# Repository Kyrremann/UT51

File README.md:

UT51
====

> Hot-swappable nordic 40% Keyboard PCB

The UT51 is a clone of the UT47.2 with an added cloumn for nordic letters. This also enables the use of the traditional
arrow keys.

Keyboard Layout Editor layout: [UT51 Layout](http://www.keyboard-layout-editor.com/#/gists/70864930e7721bd26d8b0cc32576811b)

## Diary

### [rev1] - 2020-04-10

About two weeks ago I finally sat down and created the extended UT47.2 board that I wanted to make. It was some work, as
I had messed up the footprint by updating them to a newer version. Also since I had to move all the components for the
micro controller, I had to create most of the traces a new. I've now gotten the product back from production, but
haven't had time to solder it yet.

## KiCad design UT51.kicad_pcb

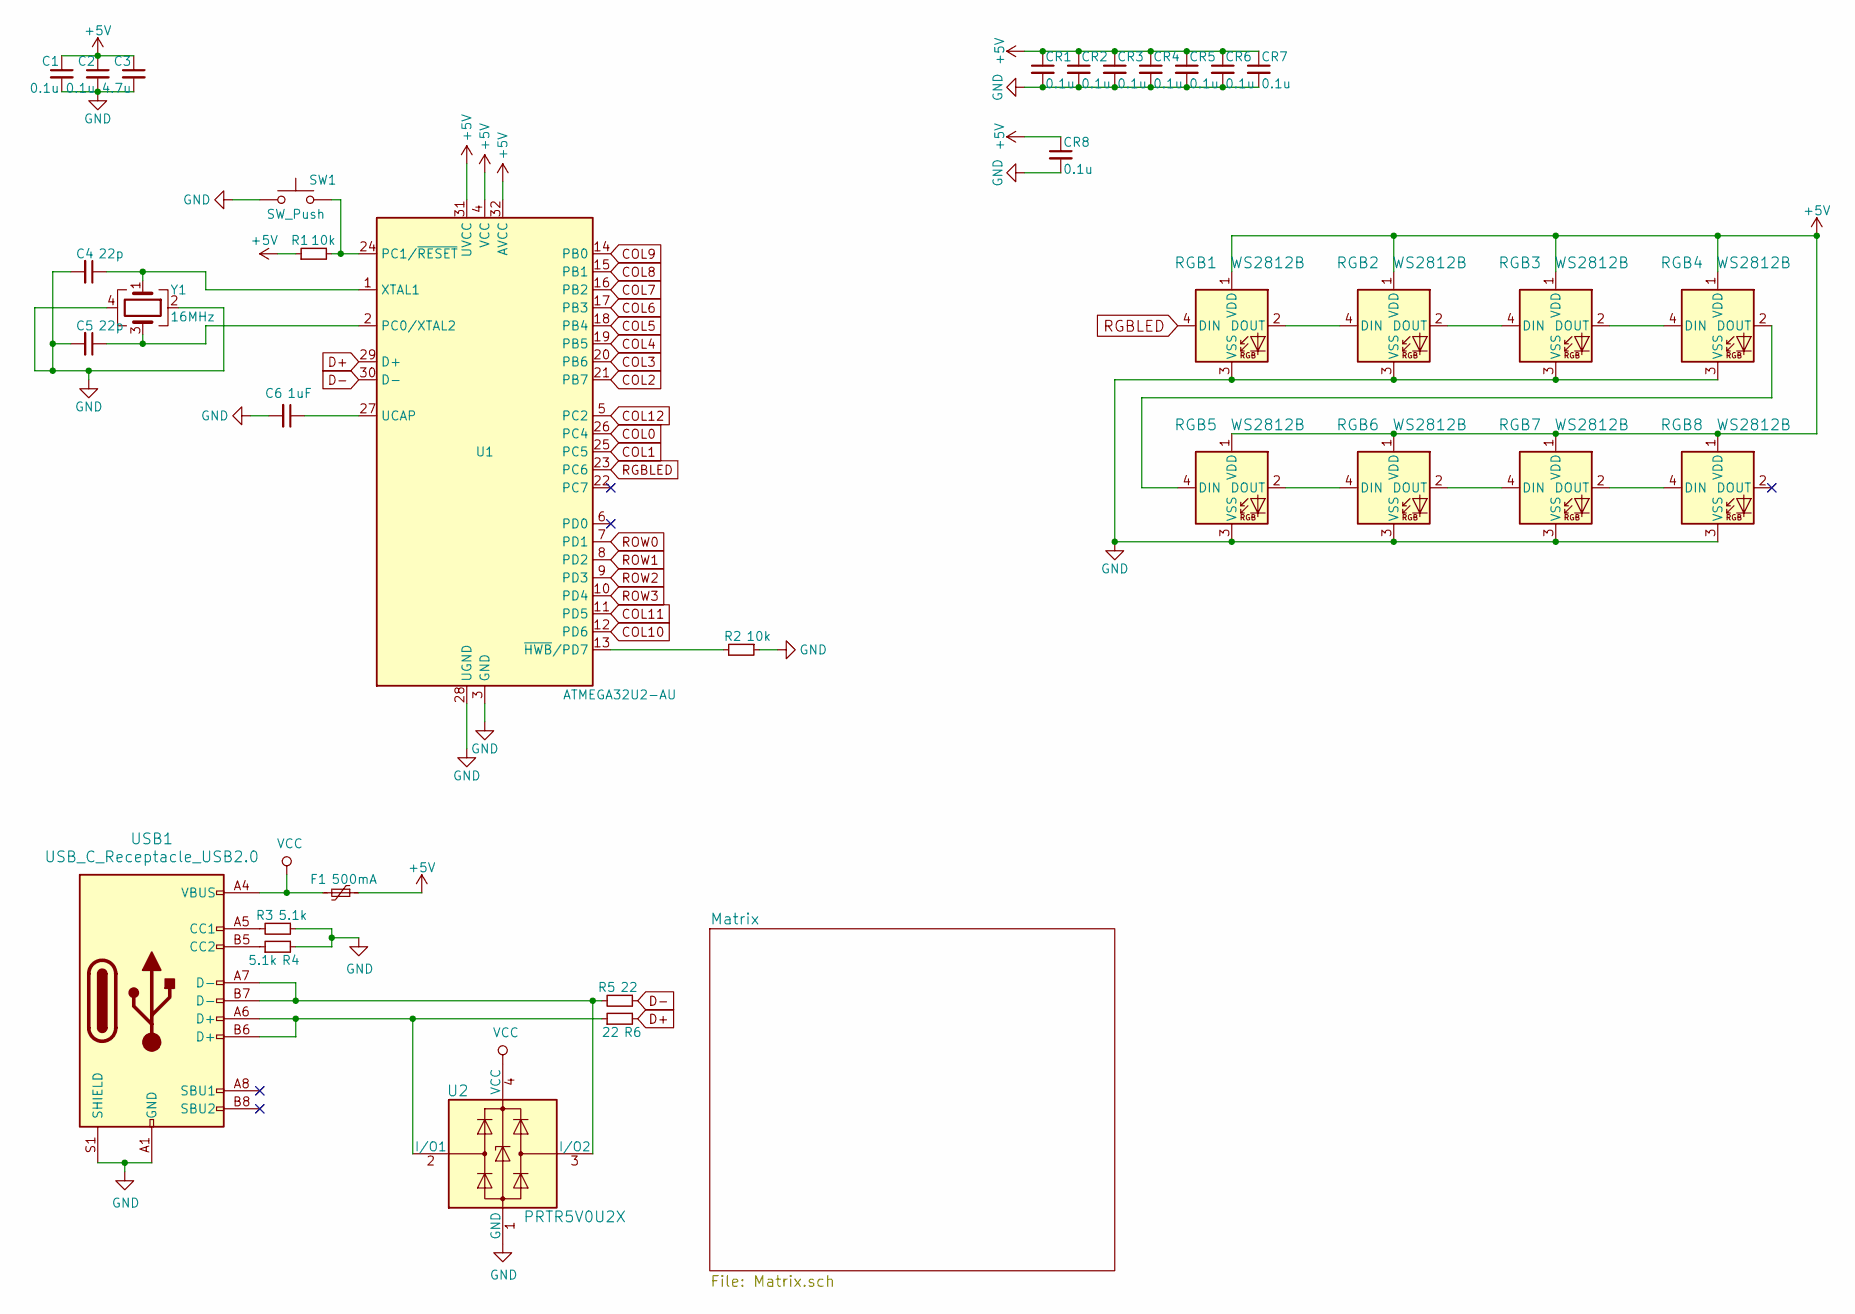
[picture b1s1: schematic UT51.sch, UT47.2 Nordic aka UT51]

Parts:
C1, C2: 0.1u; C_0603_1608Metric
C3: 4.7u; C_0603_1608Metric
C4, C5: 22p; C_0603_1608Metric
C6: 1uF; C_0603_1608Metric
CR1, CR2, CR3, CR4, CR5, CR6, CR7, CR8: 0.1u; C_0603_1608Metric
F1: 500mA; Fuse_0603_1608Metric
R1, R2: 10k; R_0603_1608Metric
R3, R4: 5.1k; R_0603_1608Metric
R5, R6: 22; R_0603_1608Metric
RGB1, RGB2, RGB3, RGB4, RGB5, RGB6, RGB7, RGB8: WS2812B; LED_WS2812B_PLCC4_5.0x5.0mm_P3.2mm
SW1: SW_Push; SW_SPST_CK_RS282G05A3
U1: ATMEGA32U2-AU; QFN-32-1EP_5x5mm_P0.5mm_EP3.1x3.1mm
U2: PRTR5V0U2X; SOT-143B
USB1: USB_C_Receptacle_USB2.0; USB_C_Receptacle_HRO_TYPE-C-31-M-12
Y1: 16MHz; Crystal_SMD_3225-4Pin_3.2x2.5mm_HandSoldering

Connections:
+5V: C1.1, C2.1, C3.1, CR1.1, CR2.1, CR3.1, CR4.1, CR5.1, CR6.1, CR7.1, CR8.1, F1.1, R1.1, RGB1.1 (VDD), RGB2.1 (VDD), RGB3.1 (VDD), RGB4.1 (VDD), RGB5.1 (VDD), RGB6.1 (VDD), RGB7.1 (VDD), RGB8.1 (VDD), U1.4 (VCC), U1.31 (UVCC), U1.32 (AVCC)
COL0: U1.26 (PC4); also elsewhere on the board
COL1: U1.25 (PC5); also elsewhere on the board
COL2: U1.21 (PB7); also elsewhere on the board
COL3: U1.20 (PB6); also elsewhere on the board
COL4: U1.19 (PB5); also elsewhere on the board
COL5: U1.18 (PB4); also elsewhere on the board
COL6: U1.17 (PB3); also elsewhere on the board
COL7: U1.16 (PB2); also elsewhere on the board
COL8: U1.15 (PB1); also elsewhere on the board
COL9: U1.14 (PB0); also elsewhere on the board
COL10: U1.12 (PD6); also elsewhere on the board
COL11: U1.11 (PD5); also elsewhere on the board
COL12: U1.5 (PC2); also elsewhere on the board
D+: R6.2, U1.29 (D+)
D-: R5.1, U1.30 (D-)
GND: C1.2, C2.2, C3.2, C4.2, C5.2, C6.2, CR1.2, CR2.2, CR3.2, CR4.2, CR5.2, CR6.2, CR7.2, CR8.2, R2.1, R3.1, R4.2, RGB1.3 (VSS), RGB2.3 (VSS), RGB3.3 (VSS), RGB4.3 (VSS), RGB5.3 (VSS), RGB6.3 (VSS), RGB7.3 (VSS), RGB8.3 (VSS), SW1.1, U1.3 (GND), U1.28 (UGND), U1.33 (GND), U2.1 (GND), USB1.A1 (GND), USB1.A12 (GND), USB1.B1 (GND), USB1.B12 (GND), USB1.S1 (SHIELD), Y1.2, Y1.4
unnamed: C4.1, U1.1 (XTAL1), Y1.1
unnamed: C5.1, U1.2 (PC0/XTAL2), Y1.3
unnamed: C6.1, U1.27 (UCAP)
unnamed: R1.2, SW1.2, U1.24 (PC1/~RESET)
unnamed: R2.2, U1.13 (~HWB~/PD7)
unnamed: R3.2, USB1.A5 (CC1)
unnamed: R4.1, USB1.B5 (CC2)
unnamed: R5.2, U2.3 (I/O2), USB1.A7 (D-), USB1.B7 (D-)
unnamed: R6.1, U2.2 (I/O1), USB1.A6 (D+), USB1.B6 (D+)
unnamed: RGB1.2 (DOUT), RGB2.4 (DIN)
unnamed: RGB2.2 (DOUT), RGB3.4 (DIN)
unnamed: RGB3.2 (DOUT), RGB4.4 (DIN)
unnamed: RGB4.2 (DOUT), RGB5.4 (DIN)
unnamed: RGB5.2 (DOUT), RGB6.4 (DIN)
unnamed: RGB6.2 (DOUT), RGB7.4 (DIN)
unnamed: RGB7.2 (DOUT), RGB8.4 (DIN)
RGBLED: RGB1.4 (DIN), U1.23 (PC6)
ROW0: U1.7 (PD1); also elsewhere on the board
ROW1: U1.8 (PD2); also elsewhere on the board
ROW2: U1.9 (PD3); also elsewhere on the board
ROW3: U1.10 (PD4); also elsewhere on the board
VCC: F1.2, U2.4 (VCC), USB1.A4 (VBUS), USB1.A9 (VBUS), USB1.B4 (VBUS), USB1.B9 (VBUS)

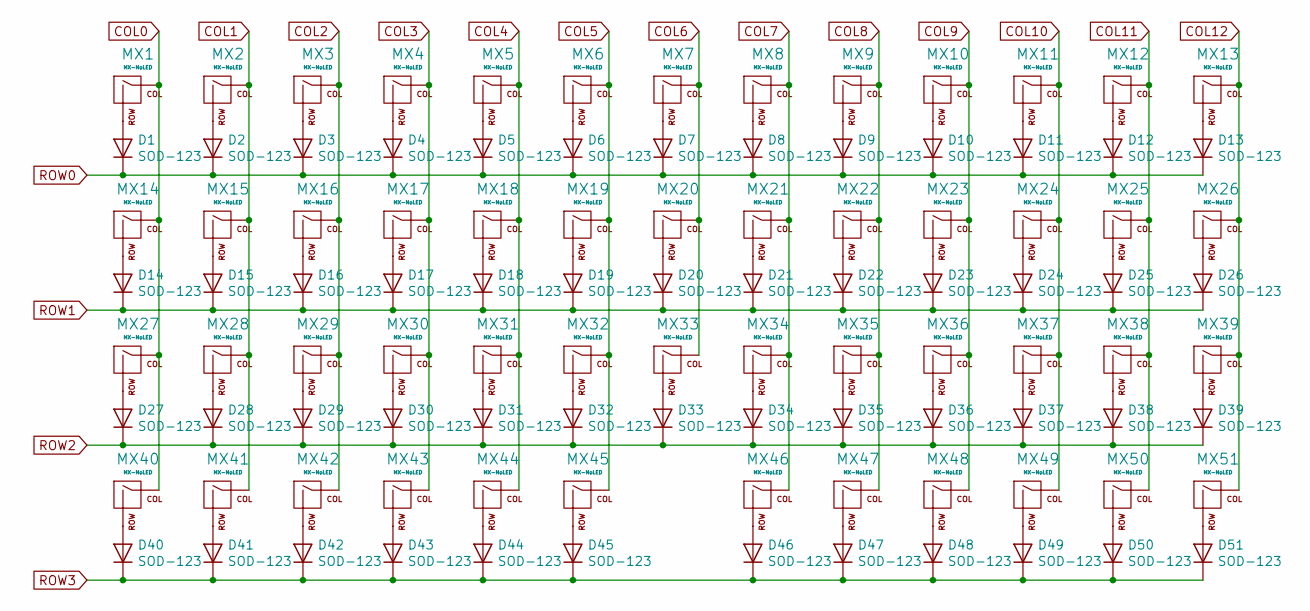
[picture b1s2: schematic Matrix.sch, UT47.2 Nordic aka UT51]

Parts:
D1, D2, D3, D4, D5, D6, D7, D8, D9, D10, D11, D12, D13, D14, D15, D16, D17, D18, D19, D20, D21, D22, D23, D24, D25, D26, D27, D28, D29, D30, D31, D32, D33, D34, D35, D36, D37, D38, D39, D40, D41, D42, D43, D44, D45, D46, D47, D48, D49, D50, D51: SOD-123; D_SOD-123
MX1, MX2, MX3, MX4, MX5, MX6, MX7, MX8, MX9, MX10, MX11, MX12, MX13, MX14, MX15, MX16, MX17, MX18, MX19, MX20, MX21, MX22, MX23, MX24, MX25, MX26, MX27, MX28, MX29, MX30, MX31, MX32, MX33, MX34, MX35, MX36, MX37, MX38, MX39, MX40, MX41, MX42, MX43, MX44, MX45, MX46, MX47, MX48, MX49, MX50, MX51: MX-NoLED; Kailh_socket_MX

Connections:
COL0: MX1.1 (COL), MX14.1 (COL), MX27.1 (COL), MX40.1 (COL); also elsewhere on the board
COL1: MX2.1 (COL), MX15.1 (COL), MX28.1 (COL), MX41.1 (COL); also elsewhere on the board
COL2: MX3.1 (COL), MX16.1 (COL), MX29.1 (COL), MX42.1 (COL); also elsewhere on the board
COL3: MX4.1 (COL), MX17.1 (COL), MX30.1 (COL), MX43.1 (COL); also elsewhere on the board
COL4: MX5.1 (COL), MX18.1 (COL), MX31.1 (COL), MX44.1 (COL); also elsewhere on the board
COL5: MX6.1 (COL), MX19.1 (COL), MX32.1 (COL), MX45.1 (COL); also elsewhere on the board
COL6: MX7.1 (COL), MX20.1 (COL), MX33.1 (COL); also elsewhere on the board
COL7: MX8.1 (COL), MX21.1 (COL), MX34.1 (COL), MX46.1 (COL); also elsewhere on the board
COL8: MX9.1 (COL), MX22.1 (COL), MX35.1 (COL), MX47.1 (COL); also elsewhere on the board
COL9: MX10.1 (COL), MX23.1 (COL), MX36.1 (COL), MX48.1 (COL); also elsewhere on the board
COL10: MX11.1 (COL), MX24.1 (COL), MX37.1 (COL), MX49.1 (COL); also elsewhere on the board
COL11: MX12.1 (COL), MX25.1 (COL), MX38.1 (COL), MX50.1 (COL); also elsewhere on the board
COL12: MX13.1 (COL), MX26.1 (COL), MX39.1 (COL), MX51.1 (COL); also elsewhere on the board
unnamed: D1.2 (A), MX1.2 (ROW)
unnamed: D2.2 (A), MX2.2 (ROW)
unnamed: D3.2 (A), MX3.2 (ROW)
unnamed: D4.2 (A), MX4.2 (ROW)
unnamed: D5.2 (A), MX5.2 (ROW)
unnamed: D6.2 (A), MX6.2 (ROW)
unnamed: D7.2 (A), MX7.2 (ROW)
unnamed: D8.2 (A), MX8.2 (ROW)
unnamed: D9.2 (A), MX9.2 (ROW)
unnamed: D10.2 (A), MX10.2 (ROW)
unnamed: D11.2 (A), MX11.2 (ROW)
unnamed: D12.2 (A), MX12.2 (ROW)
unnamed: D13.2 (A), MX13.2 (ROW)
unnamed: D14.2 (A), MX14.2 (ROW)
unnamed: D15.2 (A), MX15.2 (ROW)
unnamed: D16.2 (A), MX16.2 (ROW)
unnamed: D17.2 (A), MX17.2 (ROW)
unnamed: D18.2 (A), MX18.2 (ROW)
unnamed: D19.2 (A), MX19.2 (ROW)
unnamed: D20.2 (A), MX20.2 (ROW)
unnamed: D21.2 (A), MX21.2 (ROW)
unnamed: D22.2 (A), MX22.2 (ROW)
unnamed: D23.2 (A), MX23.2 (ROW)
unnamed: D24.2 (A), MX24.2 (ROW)
unnamed: D25.2 (A), MX25.2 (ROW)
unnamed: D26.2 (A), MX26.2 (ROW)
unnamed: D27.2 (A), MX27.2 (ROW)
unnamed: D28.2 (A), MX28.2 (ROW)
unnamed: D29.2 (A), MX29.2 (ROW)
unnamed: D30.2 (A), MX30.2 (ROW)
unnamed: D31.2 (A), MX31.2 (ROW)
unnamed: D32.2 (A), MX32.2 (ROW)
unnamed: D33.2 (A), MX33.2 (ROW)
unnamed: D34.2 (A), MX34.2 (ROW)
unnamed: D35.2 (A), MX35.2 (ROW)
unnamed: D36.2 (A), MX36.2 (ROW)
unnamed: D37.2 (A), MX37.2 (ROW)
unnamed: D38.2 (A), MX38.2 (ROW)
unnamed: D39.2 (A), MX39.2 (ROW)
unnamed: D40.2 (A), MX40.2 (ROW)
unnamed: D41.2 (A), MX41.2 (ROW)
unnamed: D42.2 (A), MX42.2 (ROW)
unnamed: D43.2 (A), MX43.2 (ROW)
unnamed: D44.2 (A), MX44.2 (ROW)
unnamed: D45.2 (A), MX45.2 (ROW)
unnamed: D46.2 (A), MX46.2 (ROW)
unnamed: D47.2 (A), MX47.2 (ROW)
unnamed: D48.2 (A), MX48.2 (ROW)
unnamed: D49.2 (A), MX49.2 (ROW)
unnamed: D50.2 (A), MX50.2 (ROW)
unnamed: D51.2 (A), MX51.2 (ROW)
ROW0: D1.1 (K), D2.1 (K), D3.1 (K), D4.1 (K), D5.1 (K), D6.1 (K), D7.1 (K), D8.1 (K), D9.1 (K), D10.1 (K), D11.1 (K), D12.1 (K), D13.1 (K); also elsewhere on the board
ROW1: D14.1 (K), D15.1 (K), D16.1 (K), D17.1 (K), D18.1 (K), D19.1 (K), D20.1 (K), D21.1 (K), D22.1 (K), D23.1 (K), D24.1 (K), D25.1 (K), D26.1 (K); also elsewhere on the board
ROW2: D27.1 (K), D28.1 (K), D29.1 (K), D30.1 (K), D31.1 (K), D32.1 (K), D33.1 (K), D34.1 (K), D35.1 (K), D36.1 (K), D37.1 (K), D38.1 (K), D39.1 (K); also elsewhere on the board
ROW3: D40.1 (K), D41.1 (K), D42.1 (K), D43.1 (K), D44.1 (K), D45.1 (K), D46.1 (K), D47.1 (K), D48.1 (K), D49.1 (K), D50.1 (K), D51.1 (K); also elsewhere on the board

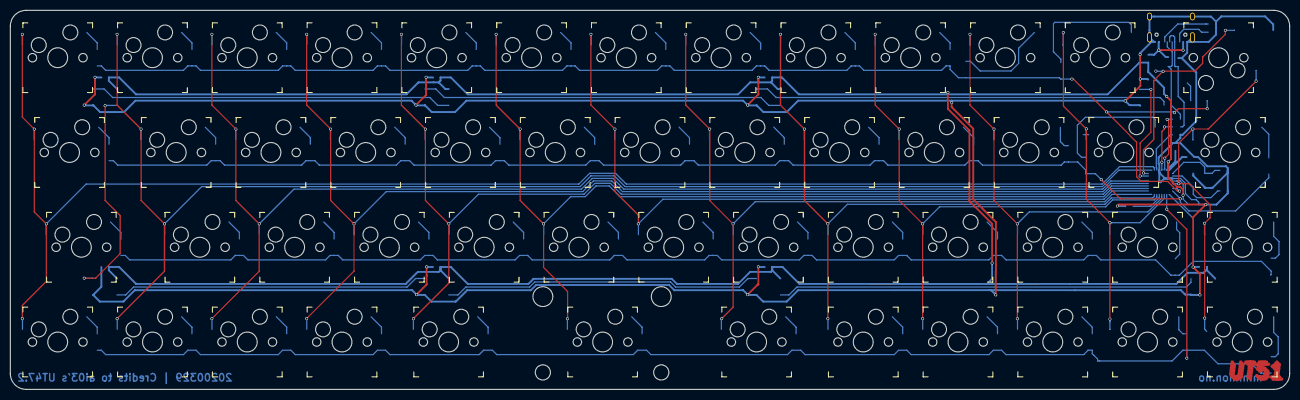
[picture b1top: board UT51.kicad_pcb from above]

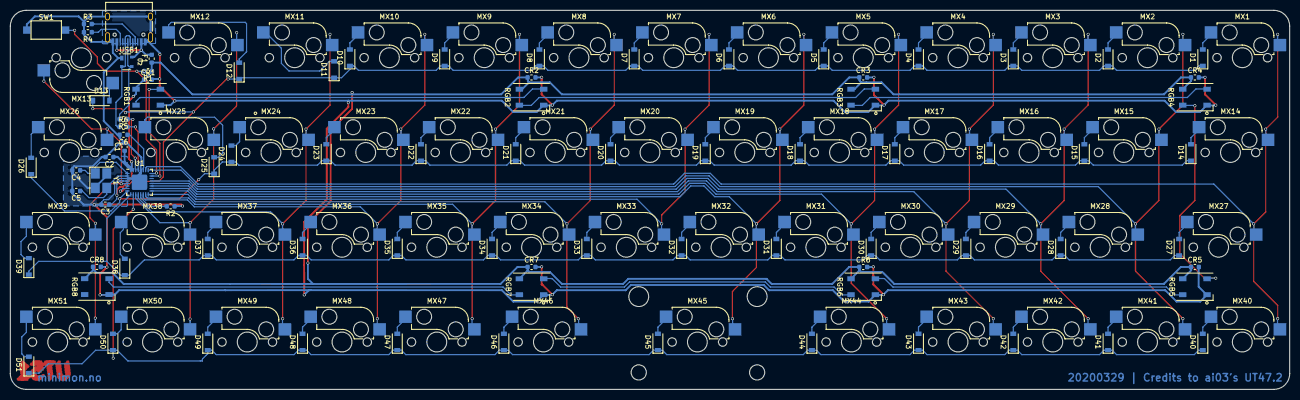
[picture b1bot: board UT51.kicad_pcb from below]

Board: 2 copper layers, 257.2 x 76.2 mm, 136 parts (85 on the bottom side), 90 nets.

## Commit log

2020-02-15 Init commit
    Updated the schematics. Next up is PCB
2020-03-04 Added the new coloumn
    Added all the needed components, just need to fix the PCB.
2020-03-29 Finished first revision
    Should be okay to order now
2020-04-10 Rev1 sent to production
2020-04-10 No need to sync DS_Store files
2020-04-10 Added a short update about rev1

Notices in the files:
README.md:
Creative Commons Attribution-ShareAlike 4.0 International License
